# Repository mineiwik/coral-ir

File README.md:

# Coral IR

## Hardware

## Software

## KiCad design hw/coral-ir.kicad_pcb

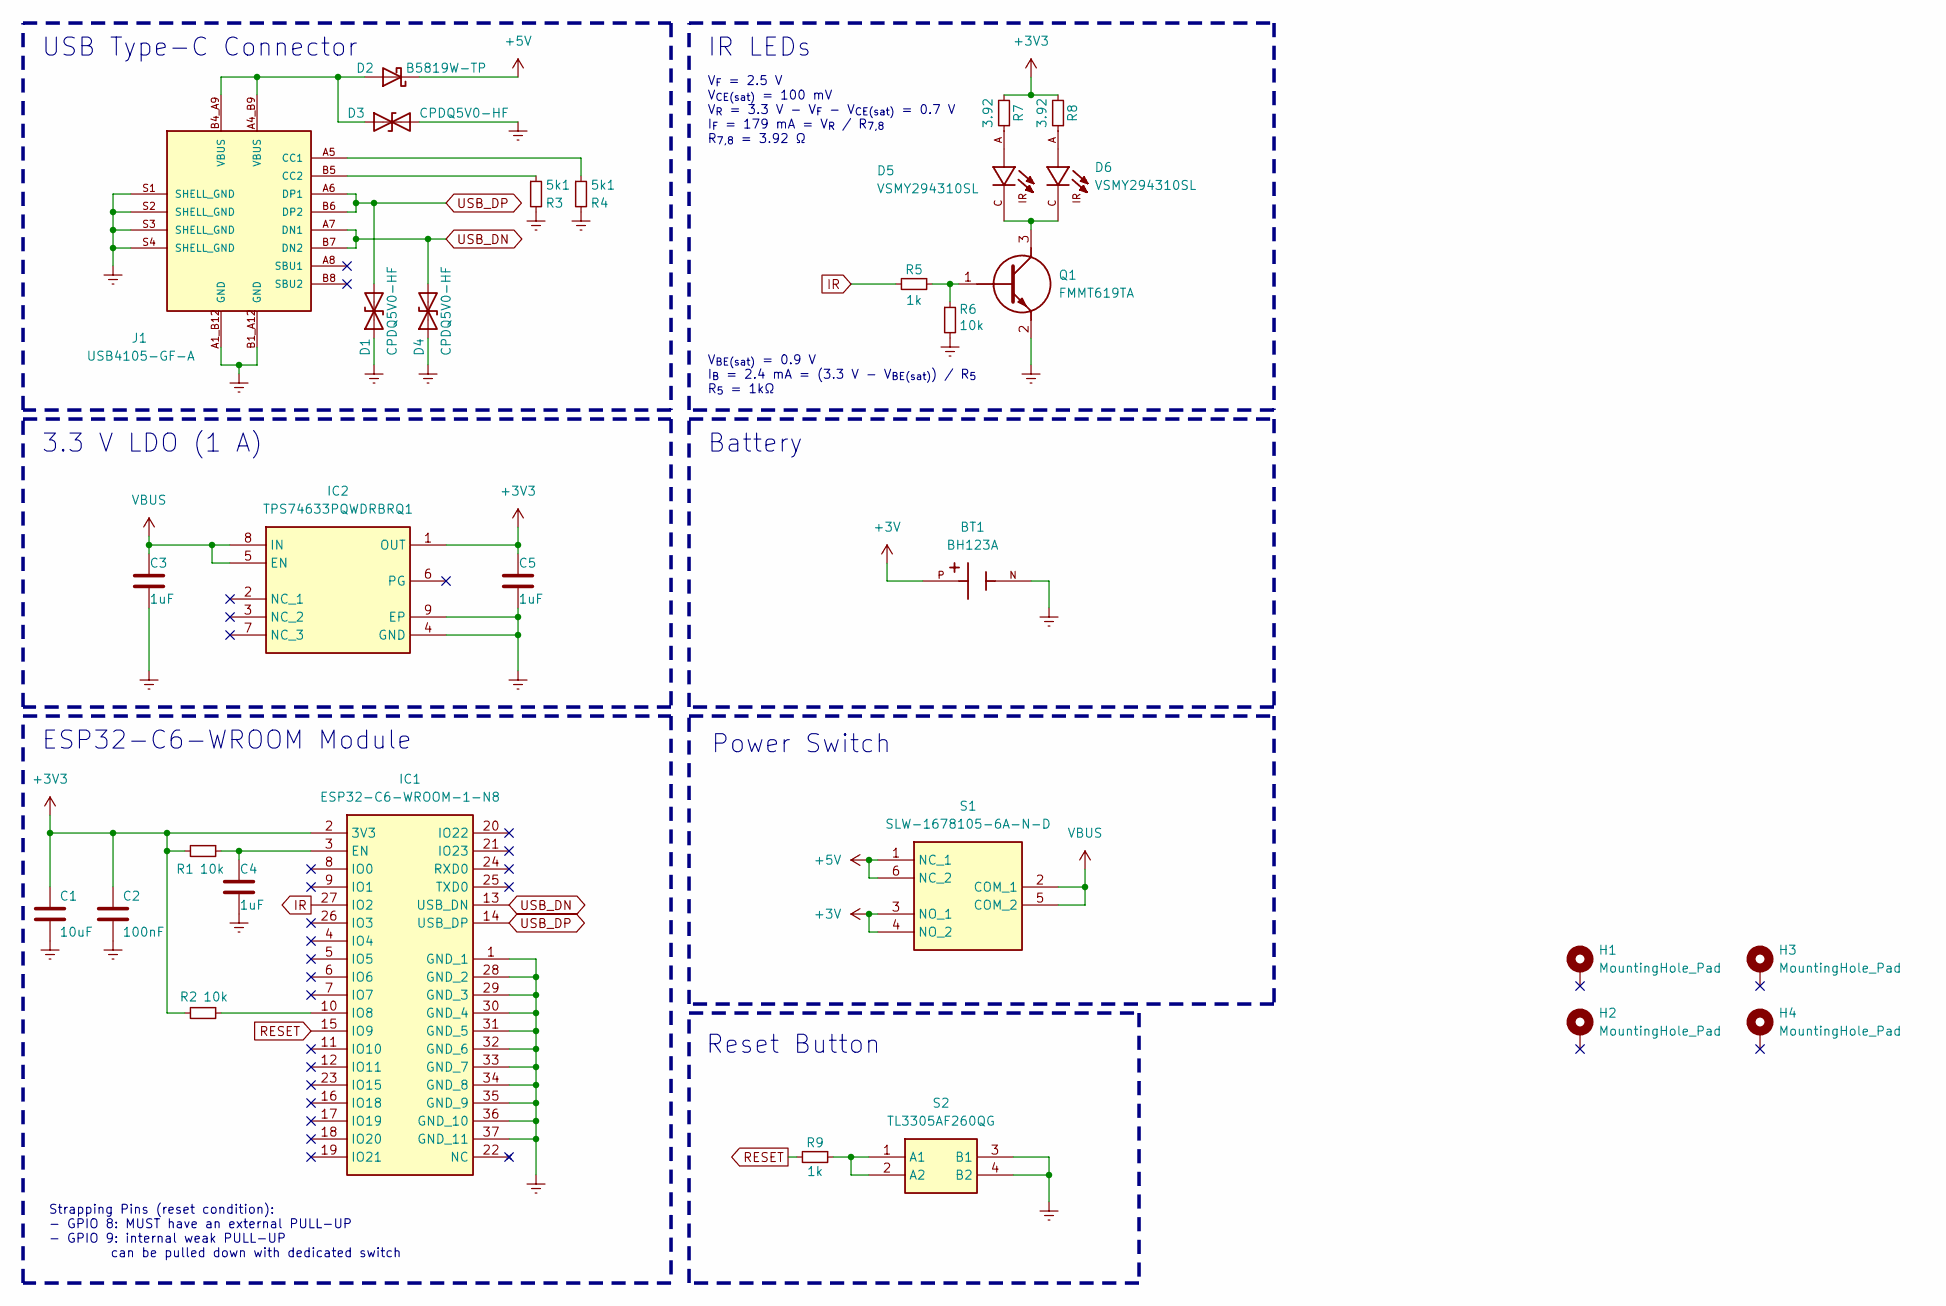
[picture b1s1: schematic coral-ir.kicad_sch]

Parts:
BT1: BH123A; BAT_BH123A; PARTREV E
C1: 10uF; Cap_Murata_GRM_0402; Manufacturer Part Number GRM155R61A106ME11D
C2: 100nF; Cap_Murata_GRM_0402; Manufacturer Part Number CC0402KRX5R9BB104
C3, C4, C5: 1uF; Cap_Murata_GRM_0402; Manufacturer Part Number CC0402KRX5R6BB105
D1, D3, D4: CPDQ5V0-HF; SODFL1006X40N; LCSC C2441615
D2: B5819W-TP; SOD3716X135N; LCSC C84354
D5, D6: VSMY294310SL; DIO_VSMY294310SL; PARTREV 1
H1, H2, H3, H4: MountingHole_Pad; MountingHole_2.2mm_M2_DIN965_Pad_TopBottom
IC1: ESP32-C6-WROOM-1-N8; ESP32C6WROOM1N8; Mouser Part Number 356-ESP32C6WROOM1N8
IC2: TPS74633PQWDRBRQ1; SON65P300X300X100-9N-D; Mouser Part Number 595-PS74633PQWDRBRQ1
J1: USB4105-GF-A; GCT_USB4105-GF-A; PARTREV A3; LCSC C3020560
Q1: FMMT619TA; SOT95P237X112-3N; Mouser Part Number 522-FMMT619TA
R1, R2, R6: 10k; R_Vishay_CRCW_0402; Manufacturer Part Number C471764
R3: 5k1; R_Vishay_CRCW_0402; Manufacturer Part Number RC0402FR-075K1L
R4: 5k1; R_Vishay_CRCW_0402; LCSC C138073
R5, R9: 1k; R_Vishay_CRCW_0402; Manufacturer Part Number RC0402FR-071KL
R7, R8: 3.92; R_Vishay_CRCW_0402
S1: SLW-1678105-6A-N-D; SLW16781056AND; Mouser Part Number 179-SLW16781056AND
S2: TL3305AF260QG; TL3305AF160QG; Mouser Part Number 612-TL3305AF260QG

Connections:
+3V: BT1.P, S1.3 (NO_1), S1.4 (NO_2)
+3V3: C1.1, C2.1, C5.1, IC1.2 (3V3), IC2.1 (OUT), R1.2, R2.2, R7.2, R8.2
+5V: D2.1 (K), S1.1 (NC_1), S1.6 (NC_2)
Earth: BT1.N, C1.2, C2.2, C3.2, C4.2, C5.2, D1.1 (A1), D3.2 (A2), D4.1 (A1), IC1.1 (GND_1), IC1.28 (GND_2), IC1.29 (GND_3), IC1.30 (GND_4), IC1.31 (GND_5), IC1.32 (GND_6), IC1.33 (GND_7), IC1.34 (GND_8), IC1.35 (GND_9), IC1.36 (GND_10), IC1.37 (GND_11), IC2.4 (GND), IC2.9 (EP), J1.A1_B12 (GND), J1.B1_A12 (GND), J1.S1 (SHELL_GND), J1.S2 (SHELL_GND), J1.S3 (SHELL_GND), J1.S4 (SHELL_GND), Q1.2 (E), R3.2, R4.2, R6.2, S2.3 (B1), S2.4 (B2)
IR: IC1.27 (IO2), R5.2
unnamed: D2.2 (A), D3.1 (A1), J1.A4_B9 (VBUS), J1.B4_A9 (VBUS)
unnamed: D5.A, R7.1
unnamed: D6.A, R8.1
unnamed: C4.1, IC1.3 (EN), R1.1
unnamed: IC1.10 (IO8), R2.1
unnamed: J1.A5 (CC1), R4.1
unnamed: J1.B5 (CC2), R3.1
unnamed: Q1.1 (B), R5.1, R6.1
unnamed: D5.C, D6.C, Q1.3 (C)
unnamed: R9.1, S2.1 (A1), S2.2 (A2)
RESET: IC1.15 (IO9), R9.2
USB_DN: D4.2 (A2), IC1.13 (USB_DN), J1.A7 (DN1), J1.B7 (DN2)
USB_DP: D1.2 (A2), IC1.14 (USB_DP), J1.A6 (DP1), J1.B6 (DP2)
VBUS: C3.1, IC2.5 (EN), IC2.8 (IN), S1.2 (COM_1), S1.5 (COM_2)

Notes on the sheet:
Strapping Pins (reset condition): - GPIO 8: MUST have an external PULL-UP - GPIO 9: internal weak PULL-UP can be pulled down with dedicated switch
Power Switch
Battery
3.3 V LDO (1 A)
IR LEDs
ESP32-C6-WROOM Module
V_{BE(sat)} = 0.9 V I_{B} = 2.4 mA = (3.3 V - V_{BE(sat)}) / R_{5} R_{5} = 1kΩ
Reset Button
V_{F} = 2.5 V V_{CE(sat)} = 100 mV V_{R} = 3.3 V - V_{F} - V_{CE(sat)} = 0.7 V I_{F} = 179 mA = V_{R} / R_{7,8} R_{7,8} = 3.92 Ω
USB Type-C Connector

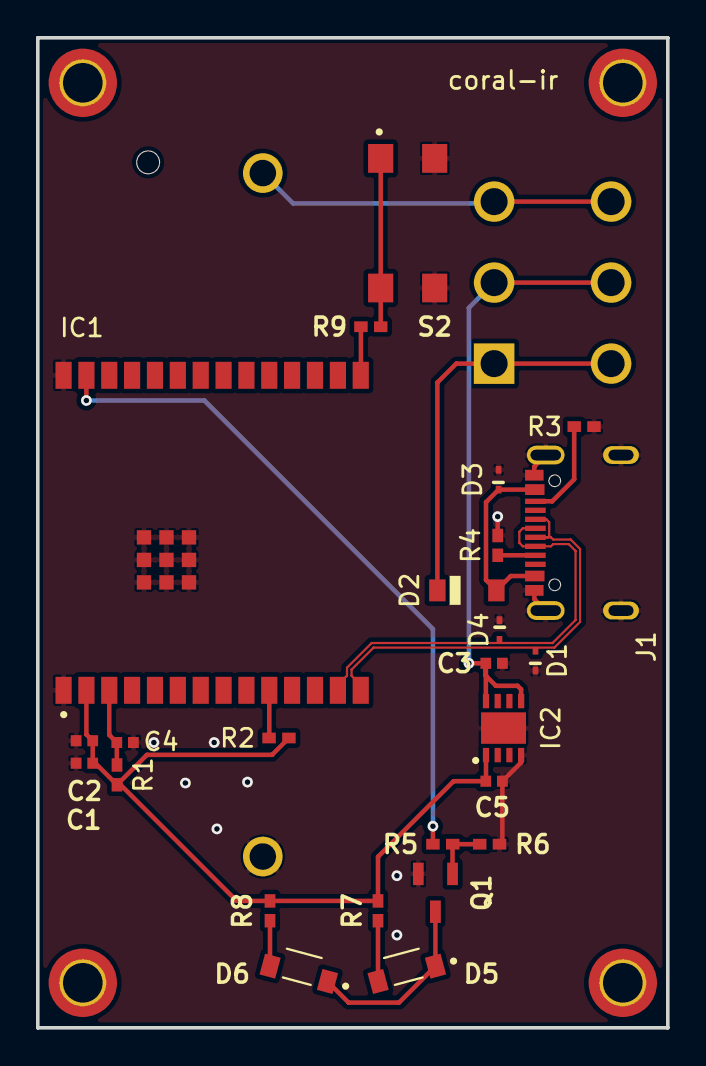
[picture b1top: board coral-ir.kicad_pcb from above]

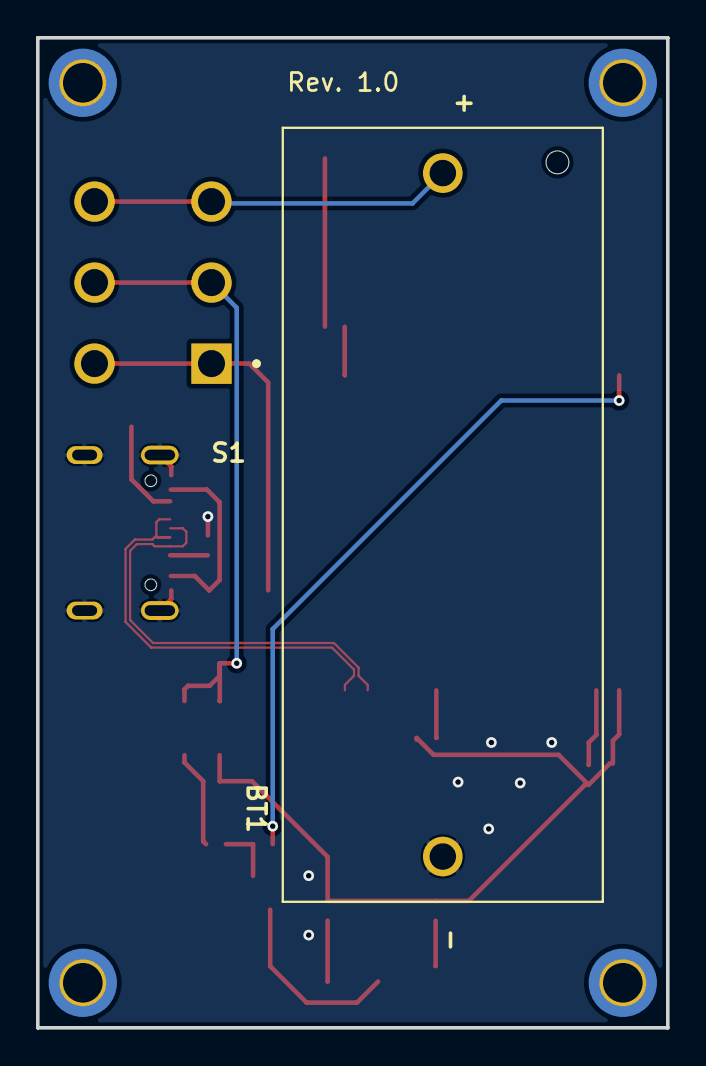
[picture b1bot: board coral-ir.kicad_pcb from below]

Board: 2 copper layers, 35.0 x 55.0 mm, 31 parts (2 on the bottom side), 19 nets.

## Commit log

2025-06-23 add fabrication outputs and schematic as PDF
2025-06-23 add assembly as PDF
2025-06-23 Finished revision 1, ready for production
